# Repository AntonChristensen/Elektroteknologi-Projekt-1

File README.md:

# Elektroteknologi-Projekt-1
Dette er starten på et fantastisk projekt

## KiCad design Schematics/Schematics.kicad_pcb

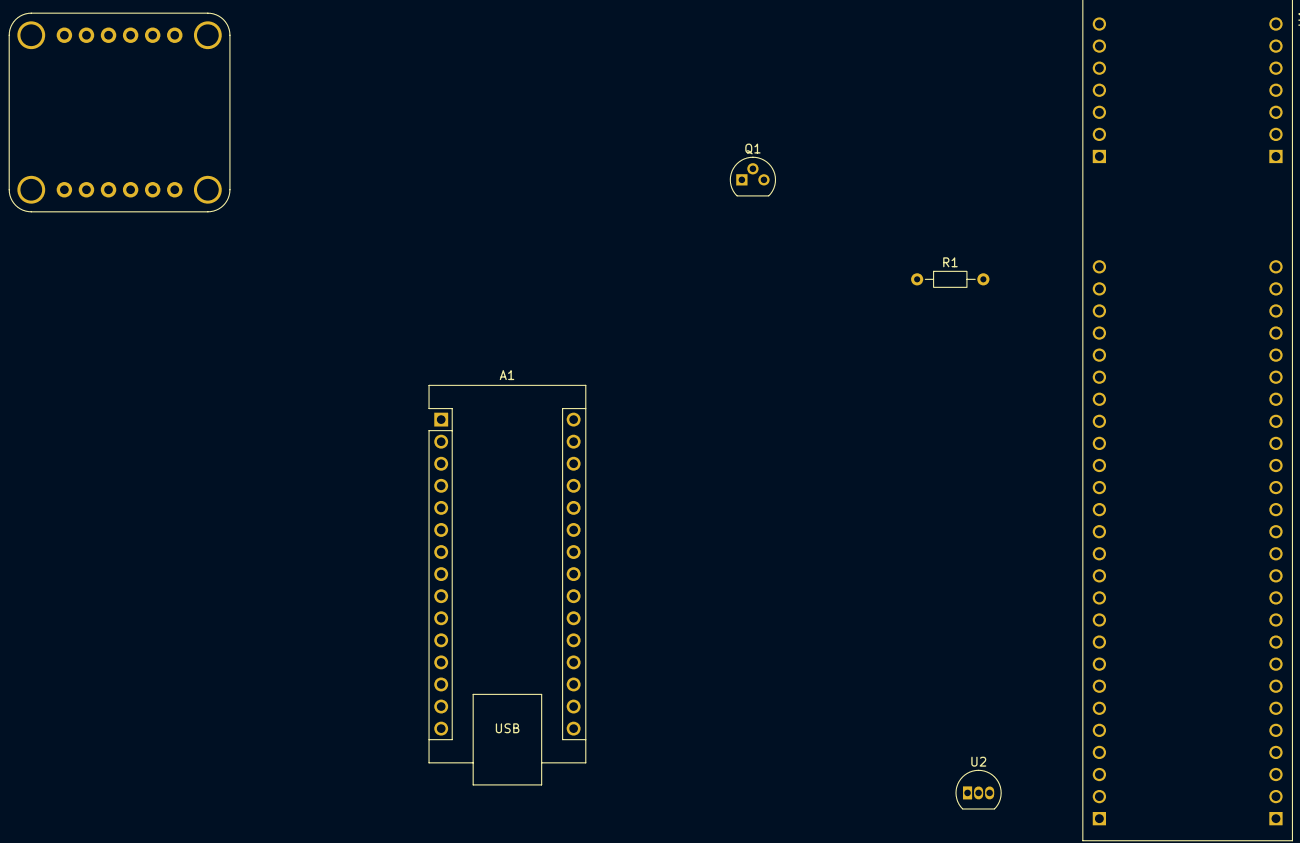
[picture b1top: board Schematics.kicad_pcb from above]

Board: 2 copper layers, 6 parts (0 on the bottom side), 8 nets, no tracks yet.

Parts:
A1: Arduino_Nano_Every; Arduino_Nano
Q1: BC547; TO-92
R1: 2.2k; R_Axial_DIN0204_L3.6mm_D1.6mm_P7.62mm_Horizontal
U1: CY8C5888LTI-LP09; MODULE_CY8CKIT-059 PSOC5
U2: LM78L05; TO-92_Inline
U3: Adafruit_BNO08x; Adafruit_BNO08x home made

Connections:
+5V: U1.J1.1 (VDD), U2.1 (VO)
+9V: A1.30 (VIN), U2.3 (VI)
/Buzzer: R1.2, U1.J2.1 (P2.0)
/I2C_SCL: A1.24 (SCL/A5), U1.J2.16 (P12.0/SCL)
/I2C_SDA: A1.23 (SDA/A4), U1.J2.15 (P12.1/SDA)
/Reset NANO: A1.3 (~RESET), U1.J2.4 (P2.3)
GND: A1.4 (GND), A1.29 (GND), Q1.3 (E), U1.J1.2 (GND), U1.J1.26 (GND), U1.J2.25 (GND), U2.2 (GND)
unnamed: Q1.2 (B), R1.1

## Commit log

2026-04-21 USBUART og forsøg på Accelerometer
2026-05-04 Buzzer
2026-05-04 Nu buzzer
2026-05-04 skrr
2026-05-04 tilføjede .gitignore
2026-05-04 edited gitignore
2026-05-04 Accelerometer virker
2026-05-06 schematic
2026-05-08 TILFØJEDE LIDT PINS
2026-05-10 blip
2026-05-10 opdaterede schematics
